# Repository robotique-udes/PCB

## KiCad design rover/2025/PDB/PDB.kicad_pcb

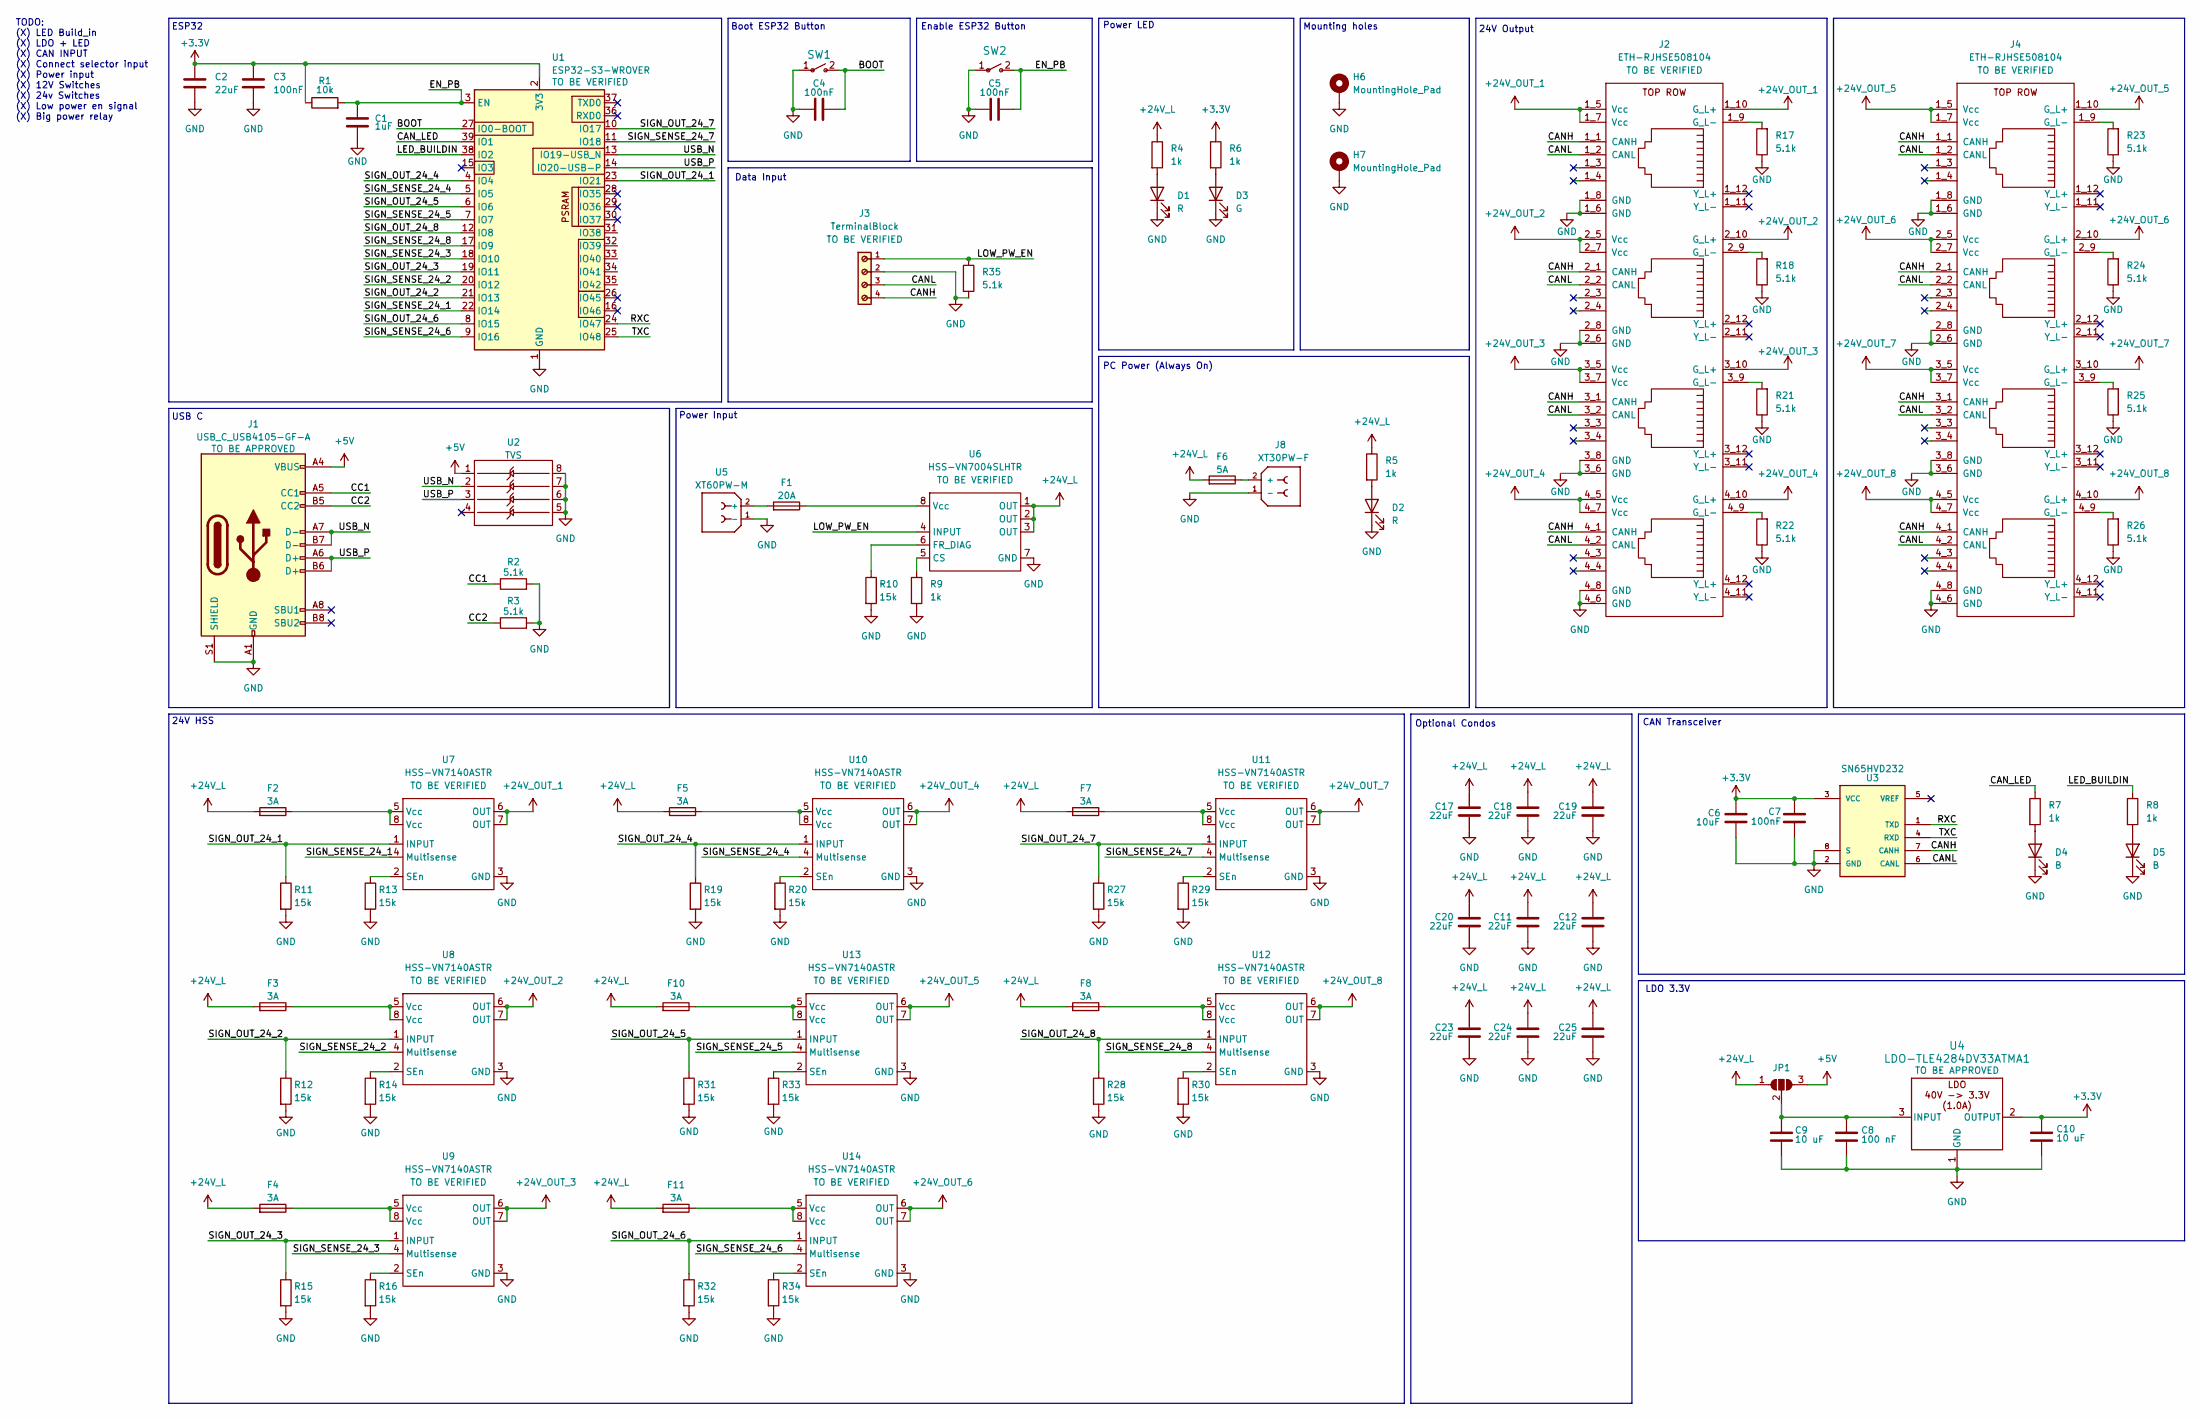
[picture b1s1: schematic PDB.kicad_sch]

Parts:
C1: 1uF; C_0805_2012Metric_Pad1.18x1.45mm_HandSolder
C2, C11, C12, C17, C18, C19, C20, C23, C24, C25: 22uF; C_0805_2012Metric_Pad1.18x1.45mm_HandSolder
C3, C4, C5, C7: 100nF; C_0805_2012Metric_Pad1.18x1.45mm_HandSolder
C6: 10uF; C_0805_2012Metric_Pad1.18x1.45mm_HandSolder
C8: 100 nF; C_0805_2012Metric_Pad1.18x1.45mm_HandSolder
C9, C10: 10 uF; C_0805_2012Metric_Pad1.18x1.45mm_HandSolder
D1, D2: R; D_0805_2012Metric_Pad1.15x1.40mm_HandSolder
D3: G; D_0805_2012Metric_Pad1.15x1.40mm_HandSolder
D4, D5: B; D_0805_2012Metric_Pad1.15x1.40mm_HandSolder
F1: 20A; FUSE_3568-20
F2, F3, F4, F5, F7, F8, F10, F11: 3A; FUSE_3568-20
F6: 5A; FUSE_3568-20
H6, H7: MountingHole_Pad; MountingHole_3.2mm_M3_DIN965_Pad_TopBottom
J1: USB_C_USB4105-GF-A; USB_C_Receptacle_HRO_TYPE-C-31-M-12
J2, J4: ETH-RJHSE508104
J3: TerminalBlock; TerminalBlock-4_P5.00mm-691137710004; PART-NUMBER 691137710004
J8: XT30PW-F; AMASS_XT30PW-F_1x02_P2.50mm_Horizontal; PARTREV 1.2
JP1: SolderJumper_3_Open; PinHeader_1x03_P2.54mm_Vertical
R1: 10k; R_0805_2012Metric_Pad1.20x1.40mm_HandSolder
R2, R3, R17, R18, R21, R22, R23, R24, R25, R26, R35: 5.1k; R_0805_2012Metric_Pad1.20x1.40mm_HandSolder
R4, R5, R6, R7, R8, R9: 1k; R_0805_2012Metric_Pad1.20x1.40mm_HandSolder
R10, R11, R12, R13, R14, R15, R16, R19, R20, R27, R28, R29, R30, R31, R32, R33, R34: 15k; R_0805_2012Metric_Pad1.20x1.40mm_HandSolder
SW1, SW2: TS09-63-25-WT-160-SMT-TR; SW_DIP_SPSTx01_Slide_6.7x4.1mm_W8.61mm_P2.54mm_LowProfile
U1: ESP32-S3-WROVER; ESP32-S3-WROOM-1U
U2: TVS; SOIC-8_3.9x4.9mm_P1.27mm
U3: SN65HVD232; SOIC-8_3.9x4.9mm_P1.27mm; PARTREV 4
U4: LDO-TLE4284DV33ATMA1; TO-252-2
U5: XT60PW-M; AMASS_XT60PW-M_1x02_P7.20mm_Horizontal
U6: HSS-VN7004SLHTR; OCTAPACK_VN7004_STM-M
U7, U8, U9, U10, U11, U12, U13, U14: HSS-VN7140ASTR; SOIC-8_3.9x4.9mm_P1.27mm

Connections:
+3.3V: C2.1, C3.1, C6.1, C7.1, C10.1, R1.1, R6.1, U1.2 (3V3), U3.3 (VCC), U4.2 (OUTPUT)
+5V: J1.A4 (VBUS), J1.A9 (VBUS), J1.B4 (VBUS), J1.B9 (VBUS), JP1.3 (B), U2.1
+24V_L: C11.1, C12.1, C17.1, C18.1, C19.1, C20.1, C23.1, C24.1, C25.1, F2.1, F3.1, F4.1, F5.1, F6.1, F7.1, F8.1, F10.1, F11.1, JP1.1 (A), R4.1, R5.1, U6.1 (OUT), U6.2 (OUT), U6.3 (OUT)
+24V_OUT_1: J2.1_5 (Vcc), J2.1_7 (Vcc), J2.1_10 (G_L+), U7.6 (OUT), U7.7 (OUT)
+24V_OUT_2: J2.2_5 (Vcc), J2.2_7 (Vcc), J2.2_10 (G_L+), U8.6 (OUT), U8.7 (OUT)
+24V_OUT_3: J2.3_5 (Vcc), J2.3_7 (Vcc), J2.3_10 (G_L+), U9.6 (OUT), U9.7 (OUT)
+24V_OUT_4: J2.4_5 (Vcc), J2.4_7 (Vcc), J2.4_10 (G_L+), U10.6 (OUT), U10.7 (OUT)
+24V_OUT_5: J4.1_5 (Vcc), J4.1_7 (Vcc), J4.1_10 (G_L+), U13.6 (OUT), U13.7 (OUT)
+24V_OUT_6: J4.2_5 (Vcc), J4.2_7 (Vcc), J4.2_10 (G_L+), U14.6 (OUT), U14.7 (OUT)
+24V_OUT_7: J4.3_5 (Vcc), J4.3_7 (Vcc), J4.3_10 (G_L+), U11.6 (OUT), U11.7 (OUT)
+24V_OUT_8: J4.4_5 (Vcc), J4.4_7 (Vcc), J4.4_10 (G_L+), U12.6 (OUT), U12.7 (OUT)
/BOOT: C4.2, SW1.2, U1.27 (IO0-BOOT)
/CANH: J2.1_1 (CANH), J2.2_1 (CANH), J2.3_1 (CANH), J2.4_1 (CANH), J3.4, J4.1_1 (CANH), J4.2_1 (CANH), J4.3_1 (CANH), J4.4_1 (CANH), U3.7 (CANH)
/CANL: J2.1_2 (CANL), J2.2_2 (CANL), J2.3_2 (CANL), J2.4_2 (CANL), J3.3, J4.1_2 (CANL), J4.2_2 (CANL), J4.3_2 (CANL), J4.4_2 (CANL), U3.6 (CANL)
/CAN_LED: R7.1, U1.39 (IO1)
/CC1: J1.A5 (CC1), R2.1
/CC2: J1.B5 (CC2), R3.1
/EN_PB: C1.1, C5.2, R1.2, SW2.2, U1.3 (EN)
/LED_BUILDIN: R8.1, U1.38 (IO2)
/LOW_PW_EN: J3.1, R35.1, U6.4 (INPUT)
/RXC: U1.24 (IO47), U3.1 (TXD)
/SIGN_OUT_24_1: R11.1, U1.23 (IO21), U7.1 (INPUT)
/SIGN_OUT_24_2: R12.1, U1.21 (IO13), U8.1 (INPUT)
/SIGN_OUT_24_3: R15.1, U1.19 (IO11), U9.1 (INPUT)
/SIGN_OUT_24_4: R19.1, U1.4 (IO4), U10.1 (INPUT)
/SIGN_OUT_24_5: R31.1, U1.6 (IO6), U13.1 (INPUT)
/SIGN_OUT_24_6: R32.1, U1.8 (IO15), U14.1 (INPUT)
/SIGN_OUT_24_7: R27.1, U1.10 (IO17), U11.1 (INPUT)
/SIGN_OUT_24_8: R28.1, U1.12 (IO8), U12.1 (INPUT)
/SIGN_SENSE_24_1: U1.22 (IO14), U7.4 (Multisense)
/SIGN_SENSE_24_2: U1.20 (IO12), U8.4 (Multisense)
/SIGN_SENSE_24_3: U1.18 (IO10), U9.4 (Multisense)
/SIGN_SENSE_24_4: U1.5 (IO5), U10.4 (Multisense)
/SIGN_SENSE_24_5: U1.7 (IO7), U13.4 (Multisense)
/SIGN_SENSE_24_6: U1.9 (IO16), U14.4 (Multisense)
/SIGN_SENSE_24_7: U1.11 (IO18), U11.4 (Multisense)
/SIGN_SENSE_24_8: U1.17 (IO9), U12.4 (Multisense)
/TXC: U1.25 (IO48), U3.4 (RXD)
/USB_N: J1.A7 (D-), J1.B7 (D-), U1.13 (IO19-USB_N), U2.2
/USB_P: J1.A6 (D+), J1.B6 (D+), U1.14 (IO20-USB-P), U2.3
GND: C1.2, C2.2, C3.2, C4.1, C5.1, C6.2, C7.2, C8.2, C9.2, C10.2, C11.2, C12.2, C17.2, C18.2, C19.2, C20.2, C23.2, C24.2, C25.2, D1.1 (K), D2.1 (K), D3.1 (K), D4.1 (K), D5.1 (K), H6.1, H7.1, J1.A1 (GND), J1.A12 (GND), J1.B1 (GND), J1.B12 (GND), J1.S1 (SHIELD), J2.1_6 (GND), J2.1_8 (GND), J2.2_6 (GND), J2.2_8 (GND), J2.3_6 (GND), J2.3_8 (GND), J2.4_6 (GND), J2.4_8 (GND), J3.2, J4.1_6 (GND), J4.1_8 (GND), J4.2_6 (GND), J4.2_8 (GND), J4.3_6 (GND), J4.3_8 (GND), J4.4_6 (GND), J4.4_8 (GND), J8.1 (-), R2.2, R3.2, R9.2, R10.2, R11.2, R12.2, R13.2, R14.2, R15.2, R16.2, R17.1, R18.1, R19.2, R20.2, R21.1, R22.1, R23.1, R24.1, R25.1, R26.1, R27.2, R28.2, R29.2, R30.2, R31.2, R32.2, R33.2, R34.2, R35.2, SW1.1, SW2.1, U1.1 (GND), U1.40 (GND), U1.41 (GND), U2.5, U2.6, U2.7, U2.8, U3.2 (GND), U3.8 (S), U4.1 (GND), U5.1 (-), U6.7 (GND), U7.3 (GND), U8.3 (GND), U9.3 (GND), U10.3 (GND), U11.3 (GND), U12.3 (GND), U13.3 (GND), U14.3 (GND)
unnamed: D1.2 (A), R4.2
unnamed: D2.2 (A), R5.2
unnamed: D3.2 (A), R6.2
unnamed: D4.2 (A), R7.2
unnamed: D5.2 (A), R8.2
unnamed: F2.2, U7.5 (Vcc), U7.8 (Vcc)
unnamed: F3.2, U8.5 (Vcc), U8.8 (Vcc)
unnamed: F4.2, U9.5 (Vcc), U9.8 (Vcc)
unnamed: F5.2, U10.5 (Vcc), U10.8 (Vcc)
unnamed: F7.2, U11.5 (Vcc), U11.8 (Vcc)
unnamed: F8.2, U12.5 (Vcc), U12.8 (Vcc)
unnamed: F10.2, U13.5 (Vcc), U13.8 (Vcc)
unnamed: F11.2, U14.5 (Vcc), U14.8 (Vcc)
unnamed: J2.1_9 (G_L-), R17.2
unnamed: J2.2_9 (G_L-), R18.2
unnamed: J2.3_9 (G_L-), R21.2
unnamed: J2.4_9 (G_L-), R22.2
unnamed: J4.1_9 (G_L-), R23.2
unnamed: J4.2_9 (G_L-), R24.2
unnamed: J4.3_9 (G_L-), R25.2
unnamed: J4.4_9 (G_L-), R26.2
unnamed: F6.2, J8.2 (+)
unnamed: C8.1, C9.1, JP1.2 (C), U4.3 (INPUT)
unnamed: F1.1, U5.2 (+)
unnamed: R9.1, U6.5 (CS)
unnamed: R10.1, U6.6 (FR_DIAG)
unnamed: F1.2, U6.8 (Vcc)
unnamed: R13.1, U7.2 (SEn)
unnamed: R14.1, U8.2 (SEn)
unnamed: R16.1, U9.2 (SEn)
unnamed: R20.1, U10.2 (SEn)
unnamed: R29.1, U11.2 (SEn)
unnamed: R30.1, U12.2 (SEn)
unnamed: R33.1, U13.2 (SEn)
unnamed: R34.1, U14.2 (SEn)

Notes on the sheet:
Boot ESP32 Button
Mounting holes
Data Input
ESP32
USB C
24V Output
CAN Transceiver
24V HSS
Power Input
TODO: (X) LED Build_in (X) LDO + LED (X) CAN INPUT (X) Connect selector input (X) Power input (X) 12V Switches (X) 24v Switches (X) Low power en signal (X) Big power relay
Enable ESP32 Button
Power LED
LDO 3.3V
Optional Condos
PC Power (Always On)

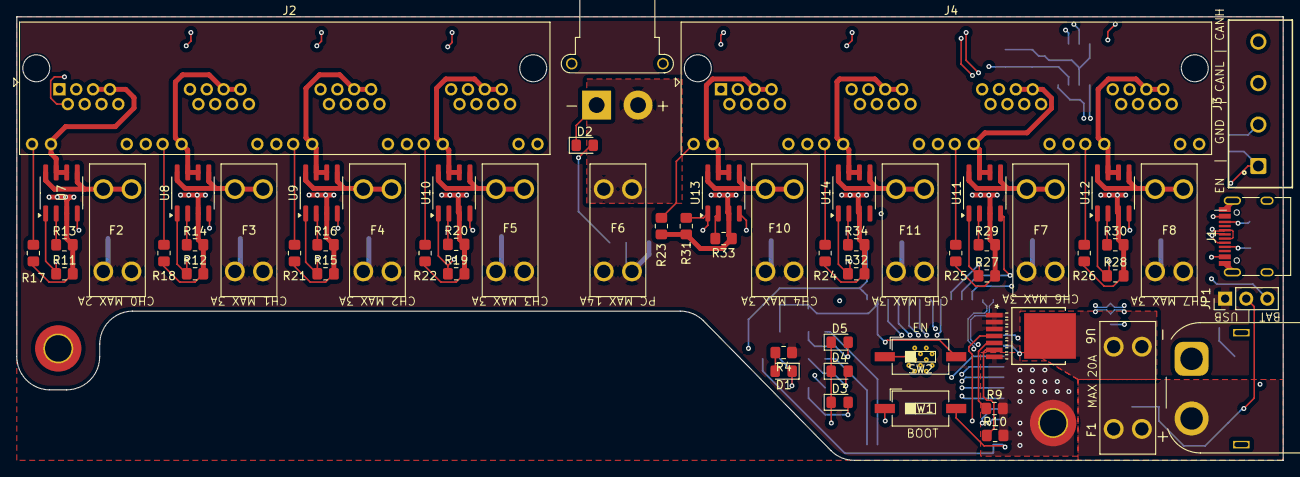
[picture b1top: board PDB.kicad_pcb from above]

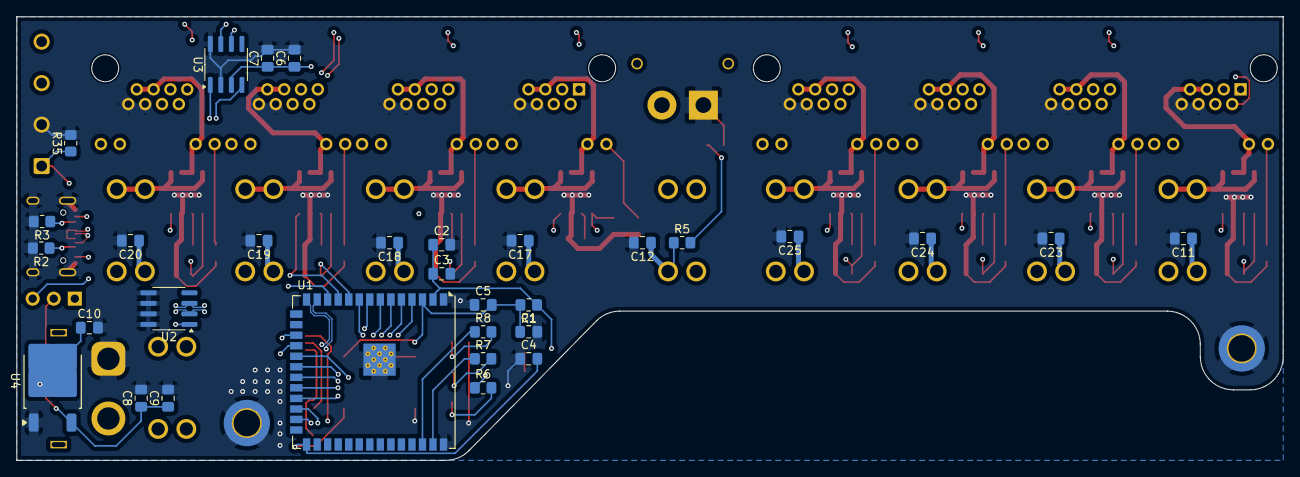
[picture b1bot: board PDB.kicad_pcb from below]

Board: 4 copper layers, 152.8 x 53.5 mm, 93 parts (31 on the bottom side), 76 nets.

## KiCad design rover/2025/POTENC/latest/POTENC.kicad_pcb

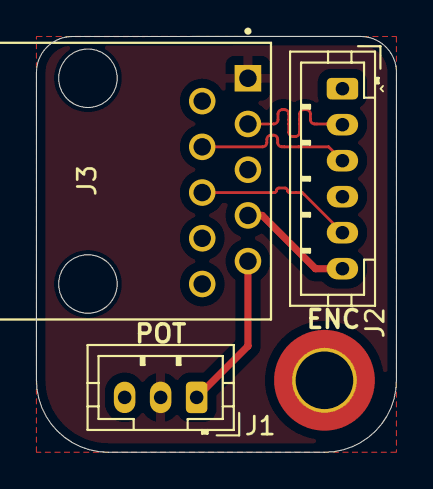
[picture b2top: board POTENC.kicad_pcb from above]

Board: 4 copper layers, 20.0 x 23.1 mm, 4 parts (0 on the bottom side), 8 nets.

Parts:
H1: MountingHole_3.2mm_M3_DIN965_Pad_TopBottom
J1: POT; JST_PH_B3B-PH-K_1x03_P2.00mm_Vertical
J2: Conn_01x06_Socket; JST_PH_B6B-PH-K_1x06_P2.00mm_Vertical
J3: RJ50-SS-641010-A-NF-A111

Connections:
+3.3V: J1.2, J3.1
+5V: J2.1, J3.2
/board/CUI_CS: J2.6, J3.7
/board/CUI_MISO: J2.5, J3.6
/board/CUI_MOSI: J2.3, J3.4
/board/CUI_SCLK: J2.2, J3.3
/board/POT_ANAL: J1.1, J3.9
GND: H1.1, J1.3, J2.4, J3.5, J3.10

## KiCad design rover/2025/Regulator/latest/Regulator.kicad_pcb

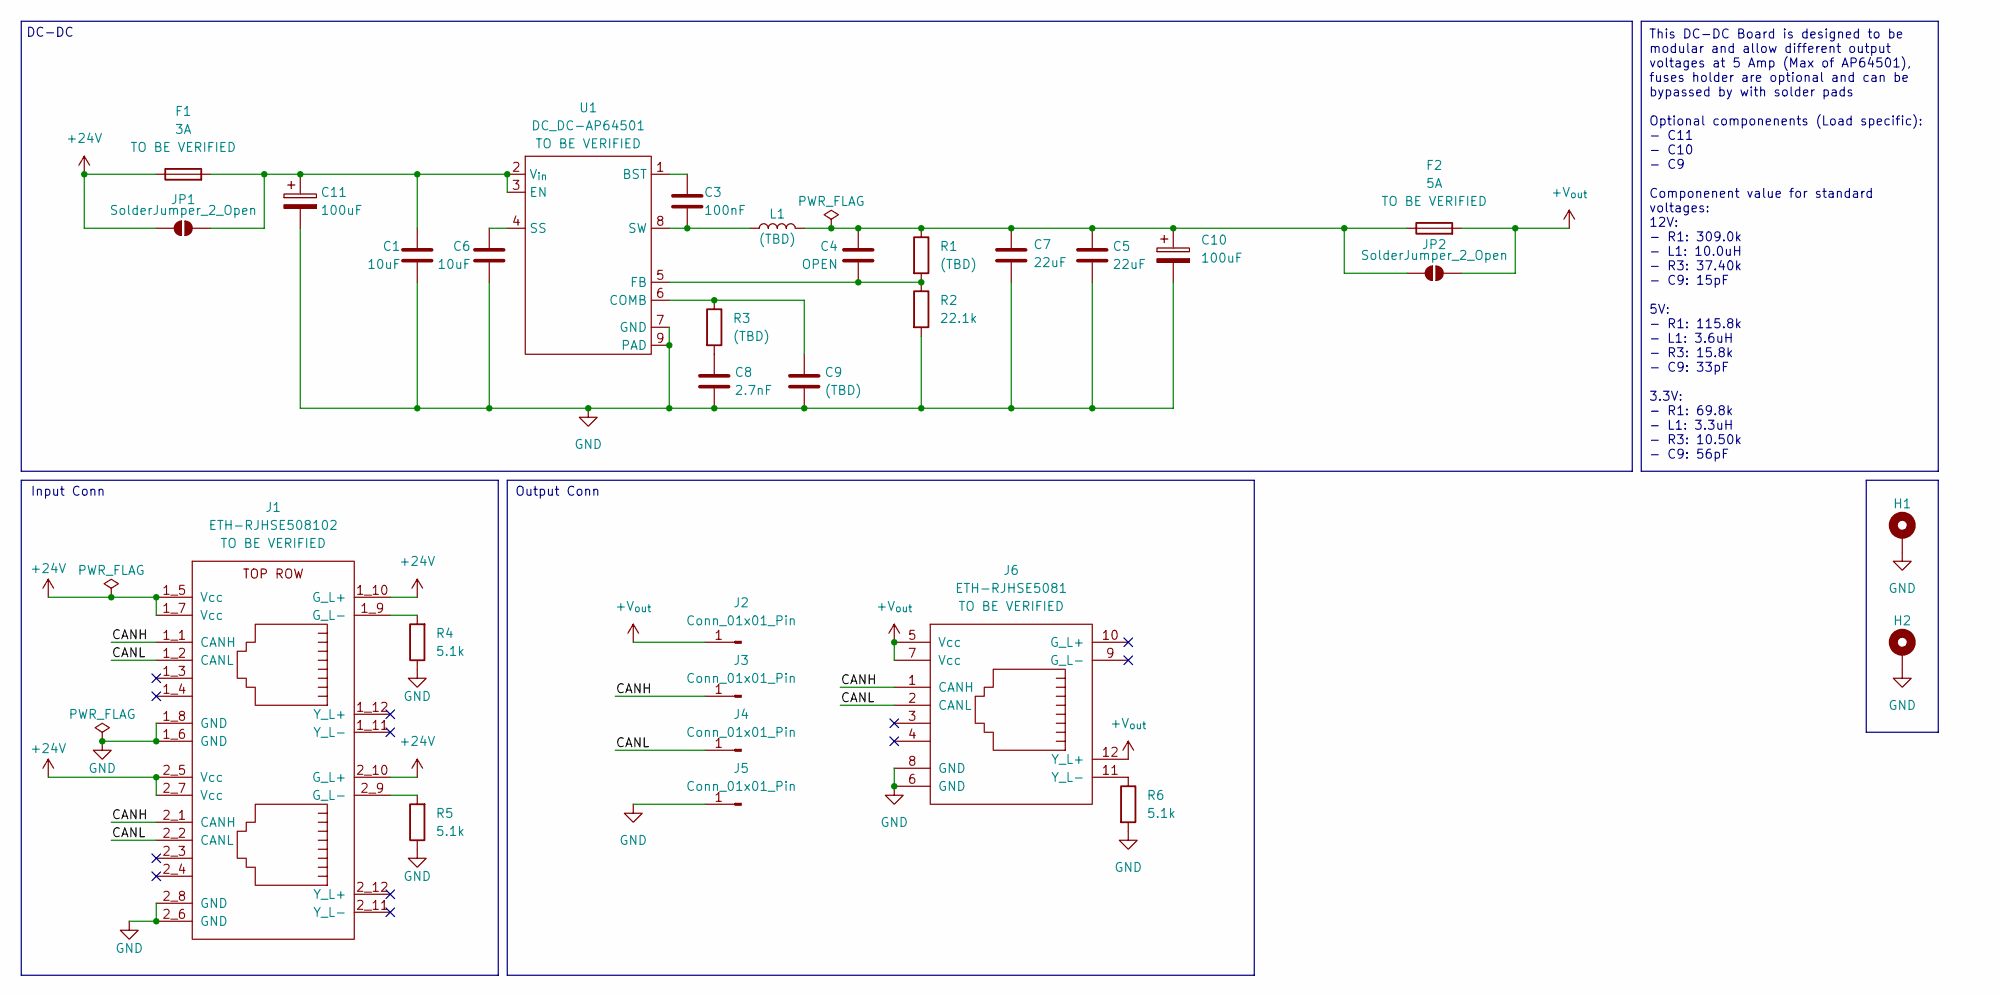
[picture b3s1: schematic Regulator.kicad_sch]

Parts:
C1, C6: 10uF; C_1210_3225Metric_Pad1.33x2.70mm_HandSolder
C3: 100nF; C_0805_2012Metric_Pad1.18x1.45mm_HandSolder
C4: OPEN; C_0805_2012Metric_Pad1.18x1.45mm_HandSolder
C5, C7: 22uF; C_1210_3225Metric_Pad1.33x2.70mm_HandSolder
C8: 2.7nF; C_0805_2012Metric_Pad1.18x1.45mm_HandSolder
C9: (TBD); C_0805_2012Metric_Pad1.18x1.45mm_HandSolder
C10, C11: 100uF; CP_Elec_6.3x7.7
F1: 3A; FuseHolder-3588-20
F2: 5A; FuseHolder-3588-20
H1, H2: MountingHole_Pad; MountingHole_3.2mm_M3_DIN965_Pad_TopBottom
J1: ETH-RJHSE508102
J2, J3, J4, J5: Conn_01x01_Pin; Pad_SMD_1x3mm
J6: ETH-RJHSE5081
JP1, JP2: SolderJumper_2_Open; SolderJumper-2_P1.3mm_Open_TrianglePad1.0x1.5mm
L1: (TBD); L_SXN_SMDRI125
R1, R3: (TBD); R_0805_2012Metric
R2: 22.1k; R_0805_2012Metric
R4, R5, R6: 5.1k; R_0805_2012Metric_Pad1.20x1.40mm_HandSolder
U1: DC_DC-AP64501; SOIC-8-1EP_3.9x4.9mm_P1.27mm_EP2.29x3mm

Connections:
+24V: F1.2, J1.1_5 (Vcc), J1.1_7 (Vcc), J1.1_10 (G_L+), J1.2_5 (Vcc), J1.2_7 (Vcc), J1.2_10 (G_L+), JP1.1 (A)
+V_{out}: F2.1, J2.1, J6.5 (Vcc), J6.7 (Vcc), J6.12 (Y_L+), JP2.2 (B)
/CANH: J1.1_1 (CANH), J1.2_1 (CANH), J3.1, J6.1 (CANH)
/CANL: J1.1_2 (CANL), J1.2_2 (CANL), J4.1, J6.2 (CANL)
GND: C1.1, C5.1, C6.1, C7.1, C8.1, C9.1, C10.2, C11.2, H1.1, H2.1, J1.1_6 (GND), J1.1_8 (GND), J1.2_6 (GND), J1.2_8 (GND), J5.1, J6.6 (GND), J6.8 (GND), R2.2, R4.1, R5.1, R6.2, U1.7 (GND), U1.9 (PAD)
unnamed: C8.2, R3.2
unnamed: J1.1_9 (G_L-), R4.2
unnamed: J1.2_9 (G_L-), R5.2
unnamed: J6.11 (Y_L-), R6.1
unnamed: C1.2, C11.1, F1.1, JP1.2 (B), U1.2 (V_{in}), U1.3 (EN)
unnamed: C4.2, C5.2, C7.2, C10.1, F2.2, JP2.1 (A), L1.2, R1.1
unnamed: C3.2, U1.1 (BST)
unnamed: C9.2, R3.1, U1.6 (COMB)
unnamed: C4.1, R1.2, R2.1, U1.5 (FB)
unnamed: C6.2, U1.4 (SS)
unnamed: C3.1, L1.1, U1.8 (SW)

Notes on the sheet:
This DC-DC Board is designed to be modular and allow different output voltages at 5 Amp (Max of AP64501), fuses holder are optional and can be bypassed by with solder pads Optional componenents (Load specific): - C11 - C10 - C9 Componenent value for standard voltages: 12V: - R1: 309.0k - L1: 10.0uH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
Input Conn
DC-DC
Output Conn

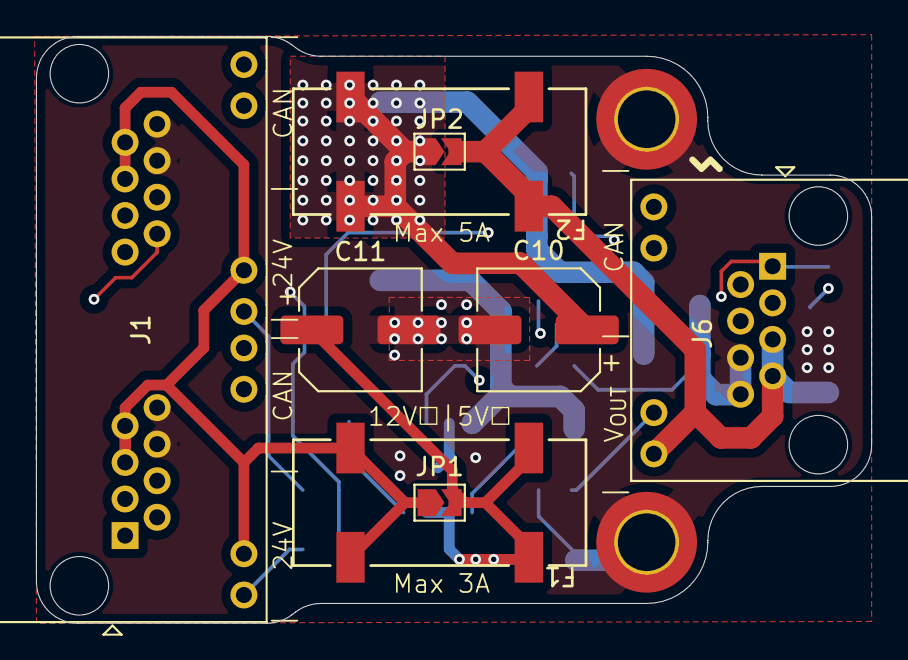
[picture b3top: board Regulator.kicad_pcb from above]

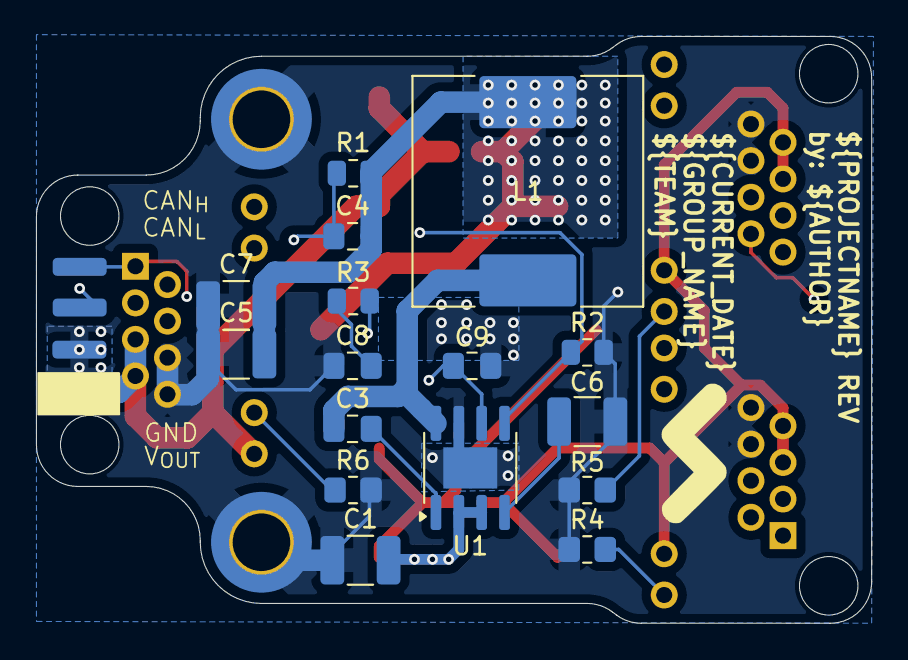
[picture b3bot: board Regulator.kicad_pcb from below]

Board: 4 copper layers, 46.4 x 32.6 mm, 30 parts (20 on the bottom side), 16 nets.

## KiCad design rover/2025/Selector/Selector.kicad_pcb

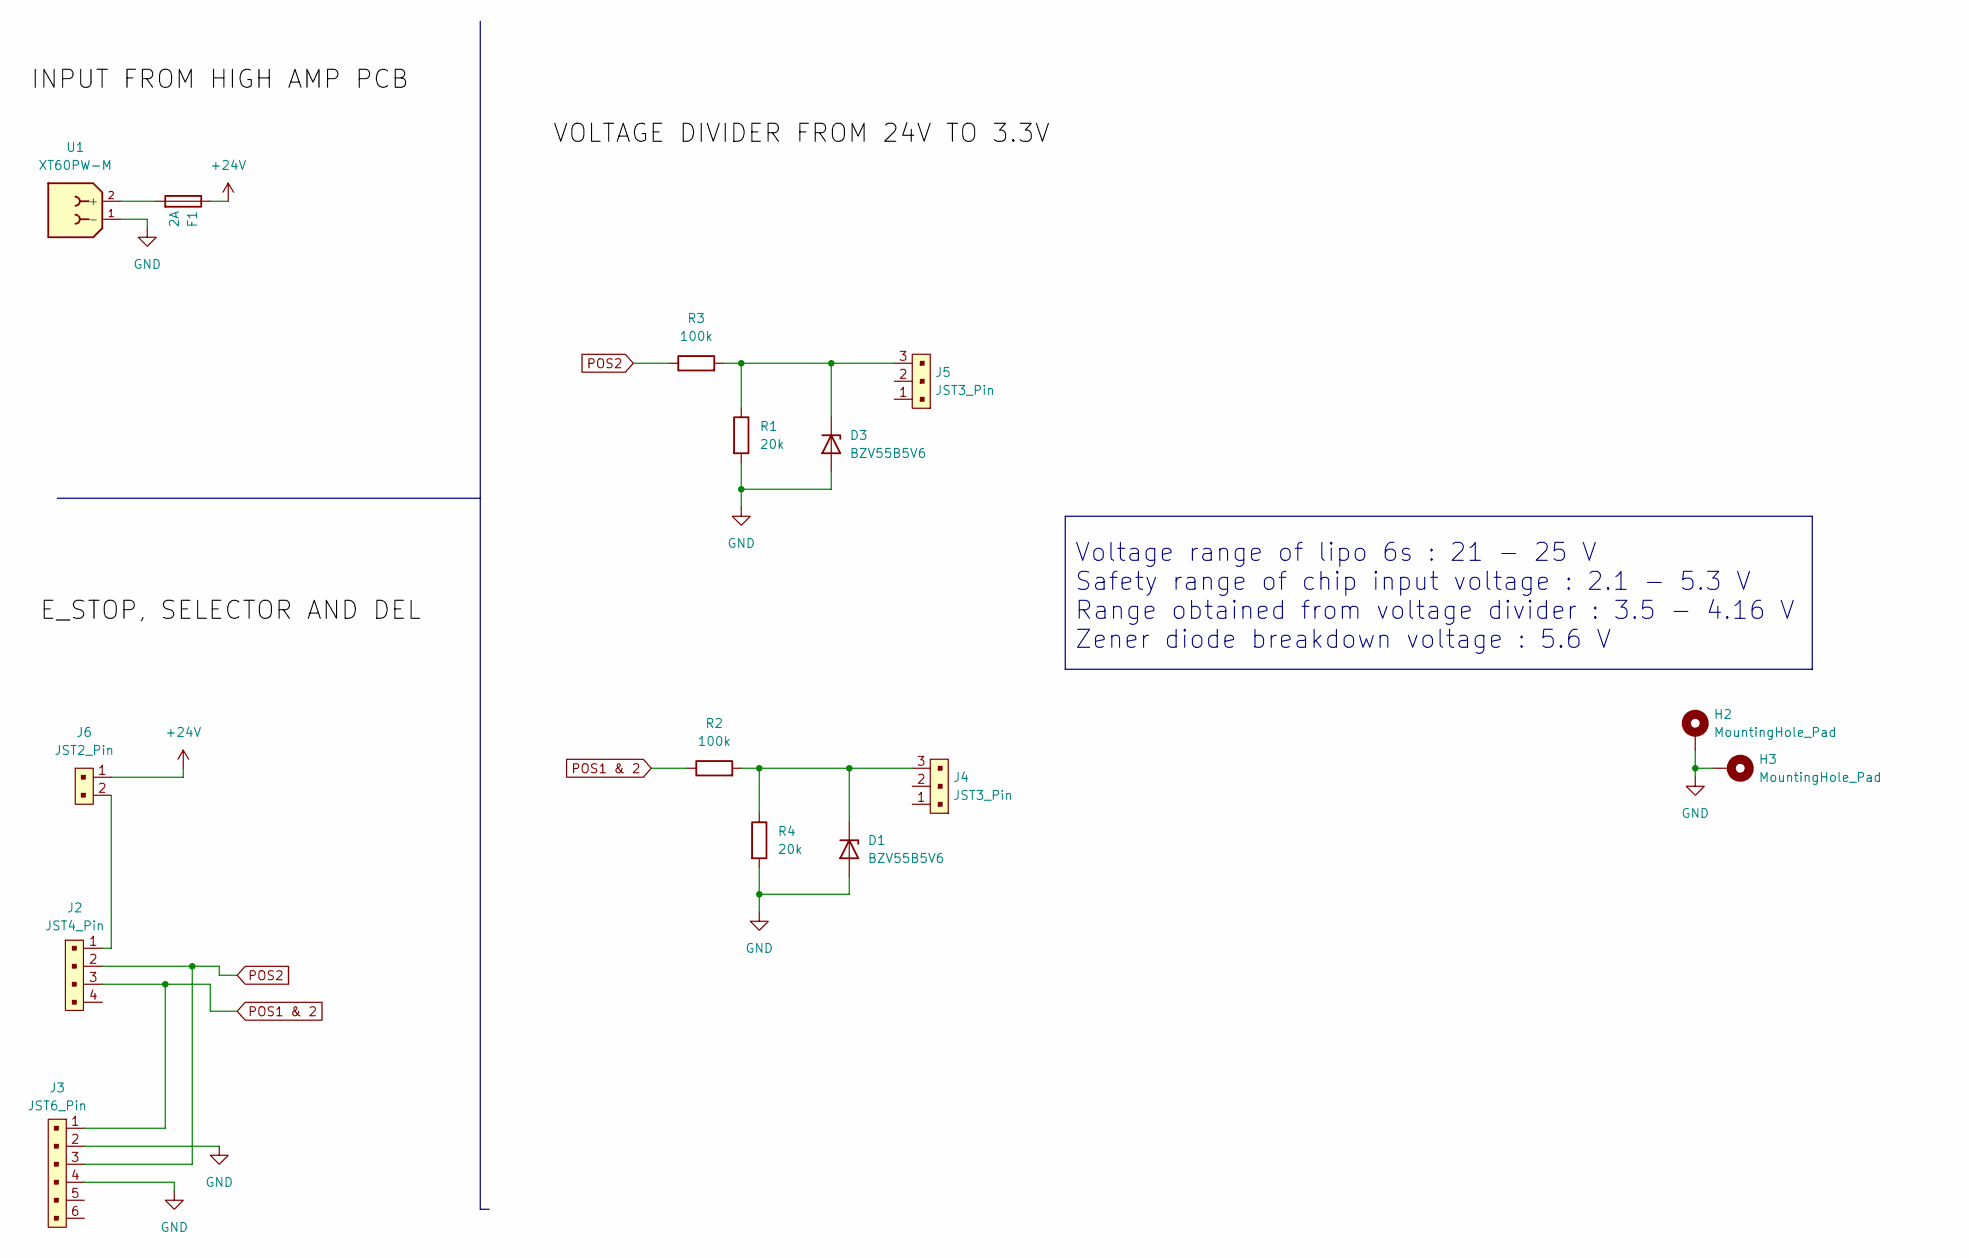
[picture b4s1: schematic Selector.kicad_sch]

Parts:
D1, D3: BZV55B5V6; D_MiniMELF
F1: 2A; FUSE_3568-20
H2, H3: MountingHole_Pad; MountingHole_3.2mm_M3_DIN965_Pad_TopBottom
J2: JST4_Pin; JST_XH_B4B-XH-A_1x04_P2.50mm_Vertical
J3: JST6_Pin; JST_XH_B6B-XH-AM_1x06_P2.50mm_Vertical
J4, J5: JST3_Pin; JST_XH_B3B-XH-AM_1x03_P2.50mm_Vertical
J6: JST2_Pin; 2-pins-JST_XH_B2B-XH-A_1x02_P2.50mm_Vertical
R1, R4: 20k; R_0805_2012Metric
R2, R3: 100k; R_0805_2012Metric
U1: XT60PW-M; AMASS_XT60PW-M_1x02_P7.20mm_Horizontal

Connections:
+24V: F1.2, J6.1; also elsewhere on the board
GND: D1.2 (A), D3.2 (A), H2.1, H3.1, J3.2, J3.4, R1.2, R4.2, U1.1 (-); also elsewhere on the board
unnamed: D1.1 (K), J4.3, R2.2, R4.1
unnamed: D3.1 (K), J5.3, R1.1, R3.2
unnamed: J2.1, J6.2
unnamed: F1.1, U1.2 (+)
POS1 & 2: J2.3, J3.1, R2.1
POS2: J2.2, J3.3, R3.1

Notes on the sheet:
Voltage range of lipo 6s : 21 - 25 V Safety range of chip input voltage : 2.1 - 5.3 V Range obtained from voltage divider : 3.5 - 4.16 V Zener diode breakdown voltage : 5.6 V

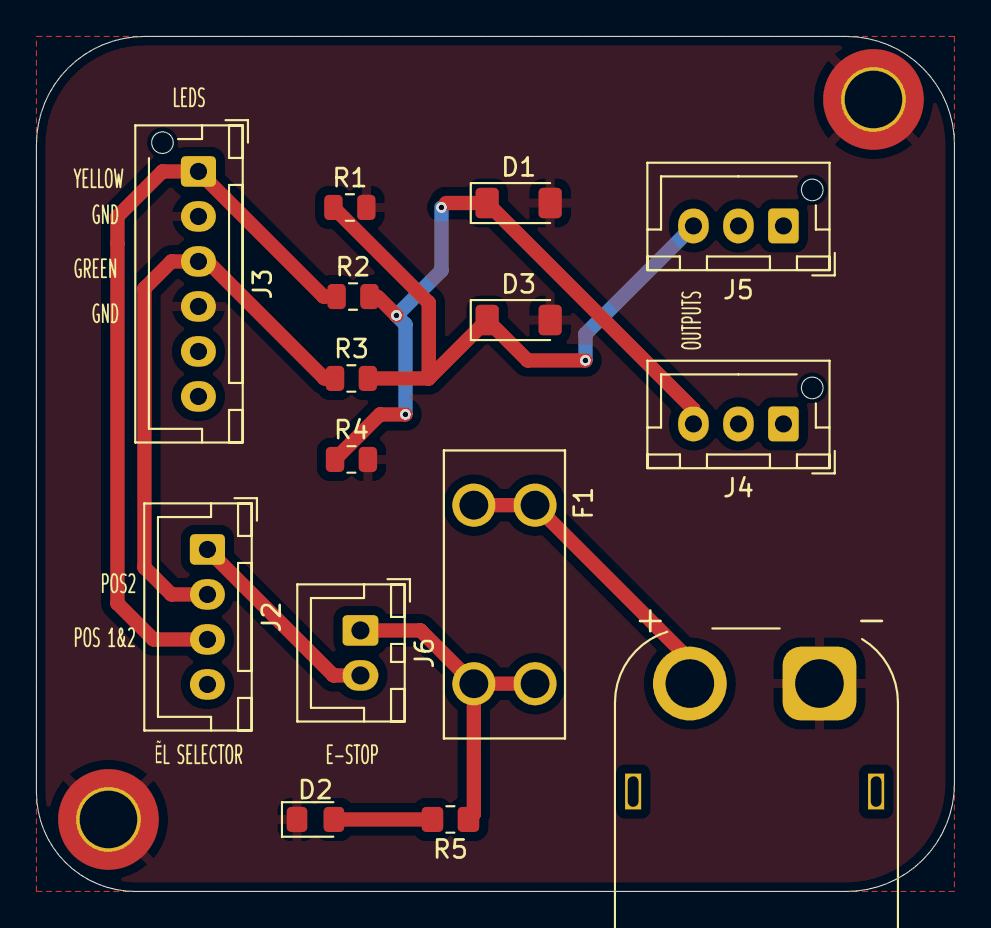
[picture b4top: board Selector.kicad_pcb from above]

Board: 2 copper layers, 51.0 x 47.5 mm, 17 parts (0 on the bottom side), 9 nets.

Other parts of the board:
D2: LED; LED_0805_2012Metric_Pad1.15x1.40mm_HandSolder
R5: 1K; R_0805_2012Metric_Pad1.20x1.40mm_HandSolder

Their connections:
+24V: R5.1; also elsewhere on the board
GND: D2.1 (K); also elsewhere on the board
unnamed: D2.2 (A), R5.2

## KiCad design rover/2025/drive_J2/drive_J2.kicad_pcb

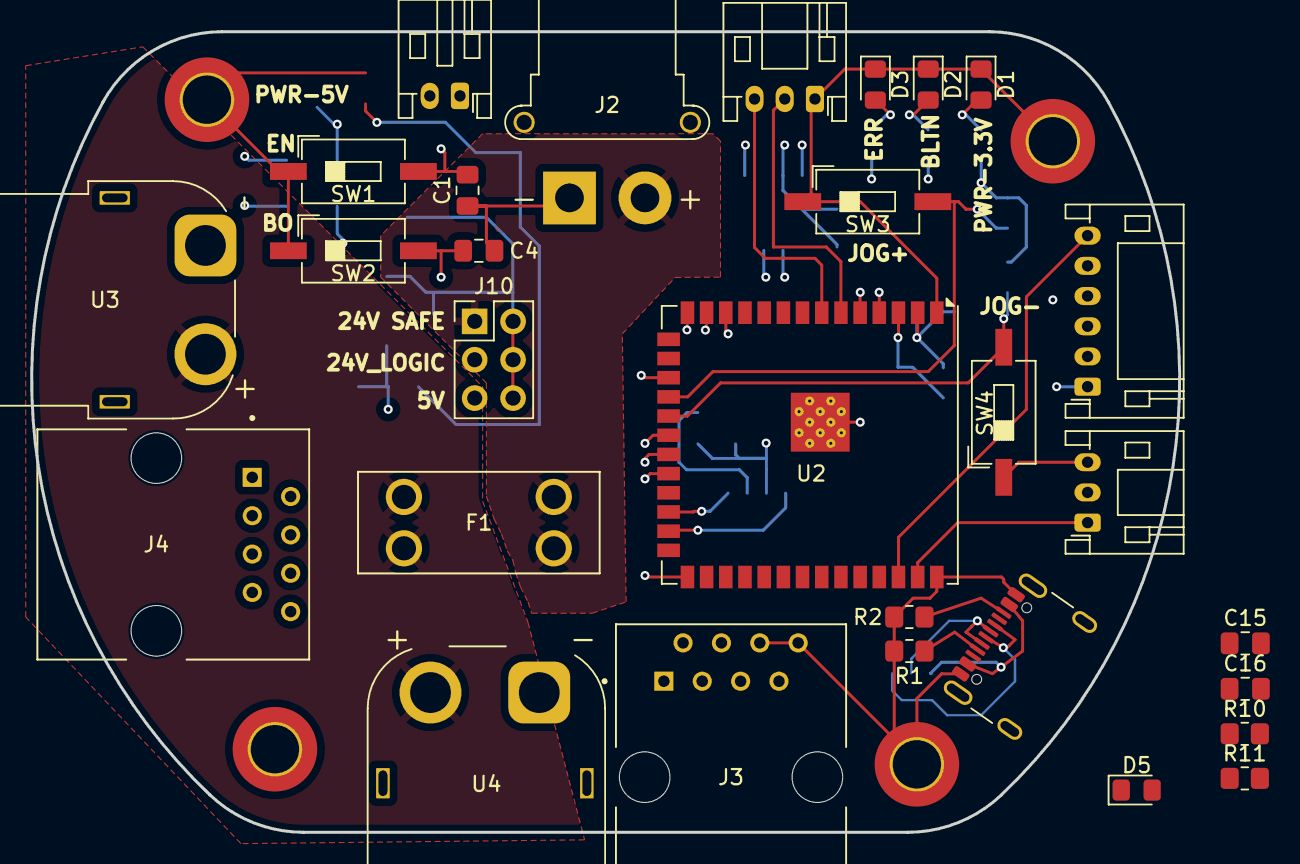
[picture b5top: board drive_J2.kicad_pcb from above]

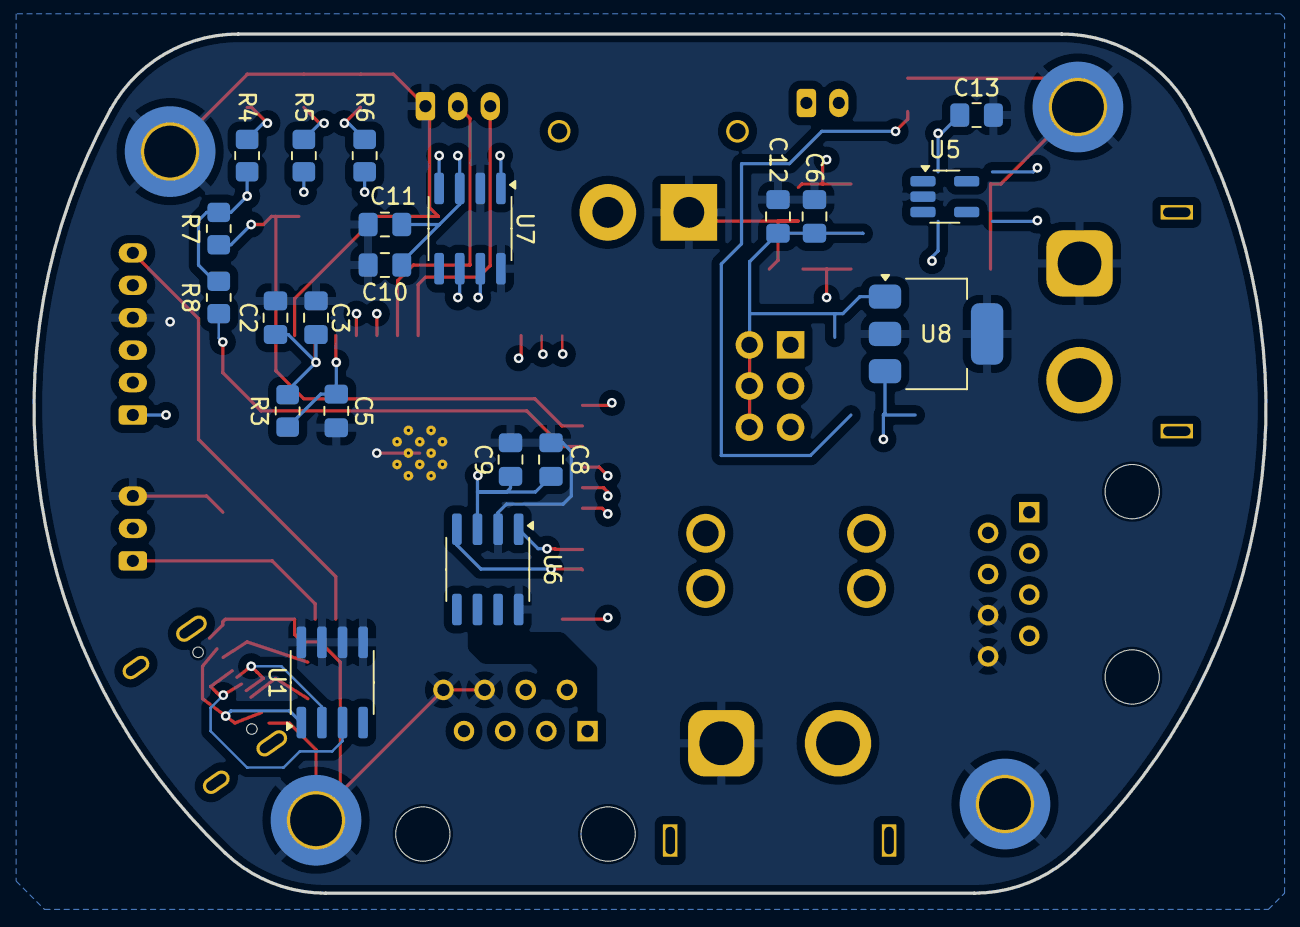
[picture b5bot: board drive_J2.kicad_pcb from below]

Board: 4 copper layers, 76.0 x 53.0 mm, 54 parts (21 on the bottom side), 37 nets.

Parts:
C1, C3, C4, C6, C9, C11, C16: 100nF; C_0805_2012Metric_Pad1.18x1.45mm_HandSolder
C2: 22uF; C_0805_2012Metric_Pad1.18x1.45mm_HandSolder
C5: 1uF; C_0805_2012Metric_Pad1.18x1.45mm_HandSolder
C8, C10, C12, C13: 10uF; C_0805_2012Metric_Pad1.18x1.45mm_HandSolder
C15: 220nF; C_0805_2012Metric_Pad1.18x1.45mm_HandSolder
D1: G; LED_0805_2012Metric_Pad1.15x1.40mm_HandSolder
D2, D3, D5: B; LED_0805_2012Metric_Pad1.15x1.40mm_HandSolder
F1: FuseHolder; FUSE_3568-20
H1, H2, H3, H4: MountingHole_Pad; MountingHole_3.2mm_M3_DIN965_Pad_TopBottom
J1: USB_C_USB4105-GF-A; USB_C_Receptacle_GCT_USB4105-xx-A_16P_TopMnt_Horizontal
J2: XT30PW-F; AMASS_XT30PW-F_1x02_P2.50mm_Horizontal
J3, J4: Eth-Horiz; Ethernet_Horizontal
J5, J8: Conn_01x03; JST_PH_S3B-PH-K_1x03_P2.00mm_Horizontal
J6: Conn_01x02; JST_PH_S2B-PH-K_1x02_P2.00mm_Horizontal
J9: Conn_01x06; JST_PH_S6B-PH-K_1x06_P2.00mm_Horizontal
J10: Jumper PWR; PinHeader_2x03_P2.54mm_Vertical
R1, R2: 5.1k; R_0805_2012Metric_Pad1.20x1.40mm_HandSolder
R3, R7, R8: 10k; R_0805_2012Metric_Pad1.20x1.40mm_HandSolder
R4, R5, R11: 1k; R_0805_2012Metric_Pad1.20x1.40mm_HandSolder
R6: 1K; R_0805_2012Metric_Pad1.20x1.40mm_HandSolder
R10: 121; R_0805_2012Metric_Pad1.20x1.40mm_HandSolder
SW1, SW2, SW3, SW4: TS09-63-25-WT-160-SMT-TR; SW_DIP_SPSTx01_Slide_6.7x4.1mm_W8.61mm_P2.54mm_LowProfile
U1: TVS-SMDB03CE3; SOIC-8_3.9x4.9mm_P1.27mm
U2: ESP32-S3-WROVER; ESP32-S3-WROOM-1U
U3: XT60PM-F; AMASS_XT60PW-F_1x02_P7.20mm_Horizontal
U4: XT60PW-M; AMASS_XT60PW-M_1x02_P7.20mm_Horizontal
U5: LDO-TLV74033PDBVR; SOT-23-5_HandSoldering
U6, U7: SN65HVD232; SOIC-8_3.9x4.9mm_P1.27mm
U8: LDO-LM7805MPX/NOPB; SOT-223-3_TabPin2

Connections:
+3.3V: C2.1, C3.1, C8.1, C9.1, C10.1, C11.1, C13.1, J8.2, R3.1, R4.1, R7.1, R8.1, U2.2 (3V3), U5.5 (OUTPUT), U6.3 (VCC), U7.3 (VCC)
+5V: C6.1, C12.1, C16.1, J9.1, J10.6, R11.1, U5.1 (INPUT), U5.3 (EN), U8.3 (OUTPUT)
+5V_USB: J1.A4 (VBUS), J1.A9 (VBUS), J1.B4 (VBUS), J1.B9 (VBUS), J10.5, U1.1
+24V: F1.2, U3.2 (+), U4.2 (+)
+24V_Logic: J3.5, J3.7, J4.5, J4.7, J10.3
+24V_safe: F1.1, J2.2 (+), J10.1
CANH_P: J3.1 (CANH), J4.1 (CANH), U6.7 (CANH)
CANL_N: J3.2 (CANL), J4.2 (CANL), U6.6 (CANL)
CAN_M_N: J6.1, R10.1
CAN_M_P: J6.2, R10.2
CUI_CS: J9.6, U2.38 (IO2)
CUI_MISO: J9.5, U2.20 (IO12)
CUI_MOSI: J9.3, U2.21 (IO13)
CUI_SCLK: J9.2, U2.22 (IO14)
EN_PB: C1.2, C5.1, R3.2, SW1.2, U2.3 (EN)
Enco_Pot: J8.1, U2.39 (IO1)
GND: C1.1, C2.2, C3.2, C4.1, C5.2, C6.2, C8.2, C9.2, C10.2, C11.2, C12.2, C13.2, C15.2, C16.2, D1.1 (K), D2.1 (K), D3.1 (K), D5.1 (K), H1.1, H2.1, H3.1, H4.1, J1.A1 (GND), J1.A12 (GND), J1.B1 (GND), J1.B12 (GND), J2.1 (-), J3.6, J3.8, J4.6, J4.8, J5.1, J8.3, J9.4, R1.2, R2.2, SW1.1, SW2.1, SW3.1, SW4.1, U1.5, U1.6, U1.7, U1.8, U2.1 (GND), U2.40 (GND), U2.41 (GND), U3.1 (-), U4.1 (-), U5.2 (GND), U6.2 (GND), U6.8 (S), U7.2 (GND), U7.8 (S), U8.2 (GND)
GPIO_0: C4.2, SW2.2, U2.27 (IO0-BOOT)
Jog+: R7.2, SW3.2, U2.18 (IO10)
Jog-: R8.2, SW4.2, U2.19 (IO11)
LED_BUILTIN: R5.1, U2.17 (IO9)
LED_ERR: R6.1, U2.12 (IO8)
unnamed: D1.2 (A), R4.2
unnamed: D2.2 (A), R5.2
unnamed: D3.2 (A), R6.2
unnamed: D5.2 (A), R11.2
unnamed: J1.A5 (CC1), R1.1
unnamed: J1.B5 (CC2), R2.1
unnamed: C15.1, J10.2, J10.4, U8.1 (INPUT)
RXC: U2.25 (IO48), U6.4 (RXD)
RXC_M: U2.4 (IO4), U7.4 (RXD)
RX_M: J5.2, U2.6 (IO6)
TXC: U2.24 (IO47), U6.1 (TXD)
TXC_M: U2.5 (IO5), U7.1 (TXD)
TX_M: J5.3, U2.7 (IO7)
USB_N: J1.A7 (D-), J1.B7 (D-), U1.2, U2.13 (IO19-USB_N)
USB_P: J1.A6 (D+), J1.B6 (D+), U1.3, U2.14 (IO20-USB-P)
